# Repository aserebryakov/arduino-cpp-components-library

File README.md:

# Support Library for Arduino Devices

## Overview

This library is meant to provide different options to use Arduino or other compatible controllers and integrate use of
different devices (rotary encoders, buttons, switches).

## Abstraction Levels

There are following levels of abstractions:

  1. Raw API
  2. Support library hardware API facade
  3. Pins
  4. Components
  5. Devices

### Raw Arduino API

Direct usage of Arduino API functions like `pinMode()`, `digitalRead()` etc.

### Support library hardware API facade

This is a facade to isolate Arduino API calls.

It provides the possibility of mocking these interfaces for the purpose of components unit testing.

```mermaid
classDiagram
    class HwApi {
        <<interface>>
        + digitalRead(...)
        + digitalWrite(...)
        + pinMode(...)
    }
```

### Pins

Abstraction level that represents pins and work with them.

```mermaid
classDiagram
    direction BT
    class PinApi {
        <<interface>>
        + begin() = 0
        + loop() = 0
    }

    class DigitalInputPin {
        + begin()
        + loop()
    }

    class DigitalOutputPin {
        + begin()
        + loop()
    }

    class AnalogInputPin {
        + begin()
        + loop()
    }

    class AnalogOutputPin {
        + begin()
        + loop()
    }

    DigitalInputPin --|> PinApi : implements
    DigitalOutputPin --|> PinApi : implements
    AnalogInputPin --|> PinApi : implements
    AnalogOutputPin --|> PinApi : implements
```

### Components

Component is a composition of pins that has clear real life functional representation:

  * encoder
  * switch
  * button
  * etc.

```mermaid
classDiagram
    direction BT
    class Component {
        <<interface>>
        + begin() = 0
        + loop() = 0
    }
    
    class DigitalInputPin {
        + begin()
        + loop()
    }

    class Button {
        + begin()
        + loop()
    }

    class RotaryEncoder {
        + ctor(dt, clk, sw)
        + begin()
        + loop()
    }

    DigitalInputPin "1" --* "1" Button
    DigitalInputPin "3" --* "1" RotaryEncoder

    class DigitalOutputPin {
        + begin()
        + loop()
    }

    class Led {
        + begin()
        + loop()
    }

    DigitalOutputPin "1" --* "1" Led
    RotaryEncoder --|> Component : implements
    Led --|> Component : implements
    Button --|> Component : implements
```

### Devices

Device is a composition of components providing a specific functionality to user (e.g. volume control, gamepad, 
mouse, etc.).

```mermaid
classDiagram
    direction BT
    
    class Device {
        <<interface>>
        + begin() = 0
        + loop() = 0
    }
    
    class VolumeControl {
        + begin()
        + loop()
    }
    
    VolumeControl --|> Device : implements
    RotaryEncoder "1" --* "1" VolumeControl
```

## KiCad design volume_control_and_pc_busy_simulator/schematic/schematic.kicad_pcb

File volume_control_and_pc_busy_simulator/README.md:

# Volume Control with PC Busy

## Idea

To build a device that will contain following functionalities:

  * Volume control (volume up, volume down, mute)
  * Mouse move emulator
  * Keyboard input emulator

## User Interface

  * 5-pin rotary encoder to control volume
  * button to turn on/off mouse move emulation (with status LED)
  * button to turn on/off keyboard input emulation (with status LED)

### Software Design

```mermaid
---
title: Rotary Encoder
---
classDiagram
    class PIN_CHANGE {
        <<enumeration>>
        LOW_HIGH,
        HIGH_LOW,
        NO_CHANGE
    }

    class RotaryEncoderPin {
        <<interface>>
        + readPinChange() PIN_CHANGE
        + readPinStatus() bool
    }

    class RotaryEncoderPinImpl {
        + ctor(number, pin_mode)
    }

    class RotaryEncoderPinMock

    class RotaryEncoder {
        + ctor(dt_pin, clk_pin, sw_pin)
        + setTurnClockwiseHandler()
        + setTurnCounterClockwiseHandler()
        + setPushButtonHandler()
        + readStatus()
        - onClockwise
        - onCounterClockwise
        - onPushButton
        - dt_pin : RotaryEncoderPin
        - clk_pin : RotaryEncoderPin
        - sw_pin : RotaryEncoderPin
    }

    PIN_CHANGE --> RotaryEncoderPin

    RotaryEncoderPin <|-- RotaryEncoderPinImpl
    RotaryEncoderPin <|-- RotaryEncoderPinMock

    RotaryEncoder *-- RotaryEncoderPin
```

### Mouse Emulator Scheduling Example

```mermaid
sequenceDiagram
    participant Scheduler
    participant Controller
    participant RotaryEncoder
    participant MouseEmulator

    loop
        Controller ->> RotaryEncoder : readStatus()
        activate RotaryEncoder
        note over RotaryEncoder : call handlers
        RotaryEncoder -->> Controller : 
        deactivate RotaryEncoder

        Controller ->> MouseEmulator : readStatus()
        activate MouseEmulator

        alt START
            MouseEmulator -->> Controller : 
            Controller ->> Scheduler : addTask(mouse_callback)
            Scheduler -->> Controller : 
        else STOP
            MouseEmulator -->> Controller : 
            deactivate MouseEmulator
            Controller ->> Scheduler : removeTask(mouse_callback)
            Scheduler -->> Controller : 
        end
        
        Controller ->> Scheduler : tick(10ms)
        Scheduler -->> Controller : 
        
        note over Controller : delay(10ms)
    end
```

### Scheduler

```mermaid
sequenceDiagram
    participant Controller
    participant Scheduler

    Controller ->> Scheduler : addPeriodicTask(callback, period)

    Scheduler -->> Controller : task id
    note over Scheduler : store callback
    note over Scheduler : store period as time to next call

    Controller ->> Scheduler : tick(interval)
    note over Scheduler : substract value from task

    alt expired
        note over Scheduler : call callback and reset period
    else
        note over Scheduler : do nothing
    end

    Scheduler -->> Controller : 
```

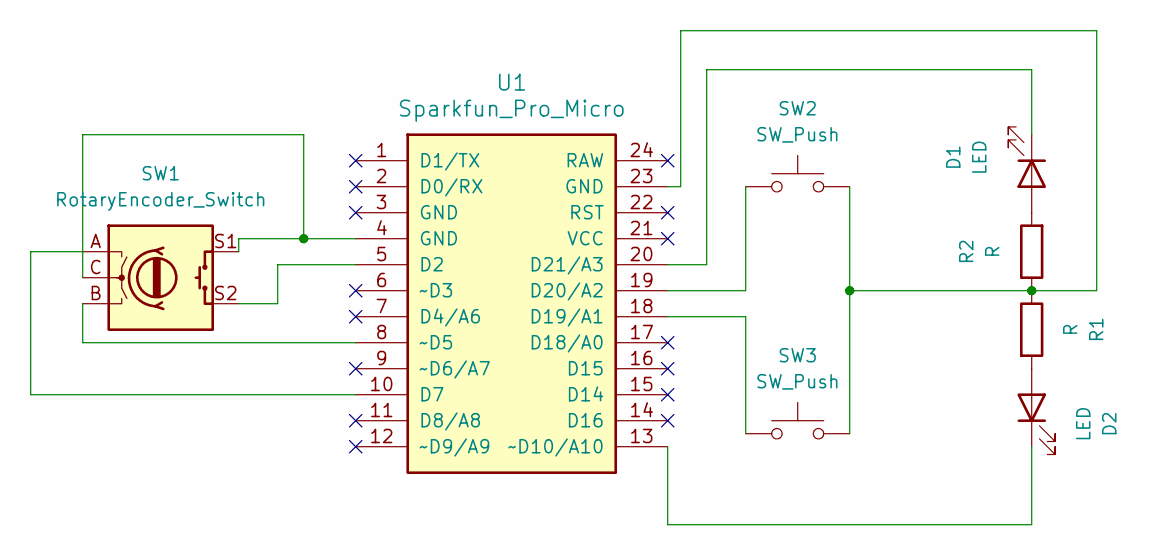
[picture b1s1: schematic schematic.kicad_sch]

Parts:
D1, D2: LED; LED_D5.0mm
R1, R2: R; R_Axial_DIN0207_L6.3mm_D2.5mm_P7.62mm_Horizontal
SW1: RotaryEncoder_Switch; RotaryEncoder_Alps_EC12E-Switch_Vertical_H20mm
SW2, SW3: SW_Push; SW_PUSH_6mm_H5mm
U1: Sparkfun_Pro_Micro

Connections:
unnamed: D1.2 (A), R2.2
unnamed: D1.1 (K), U1.20 (D21/A3)
unnamed: D2.2 (A), R1.2
unnamed: D2.1 (K), U1.13 (~D10/A10)
unnamed: R1.1, R2.1, SW2.2, SW3.2, U1.23 (GND)
unnamed: SW1.C, SW1.S1, U1.4 (GND)
unnamed: SW1.S2, U1.5 (D2)
unnamed: SW1.A, U1.10 (D7)
unnamed: SW3.1, U1.18 (D19/A1)
unnamed: SW2.1, U1.19 (D20/A2)
unnamed: SW1.B, U1.8 (~D5)

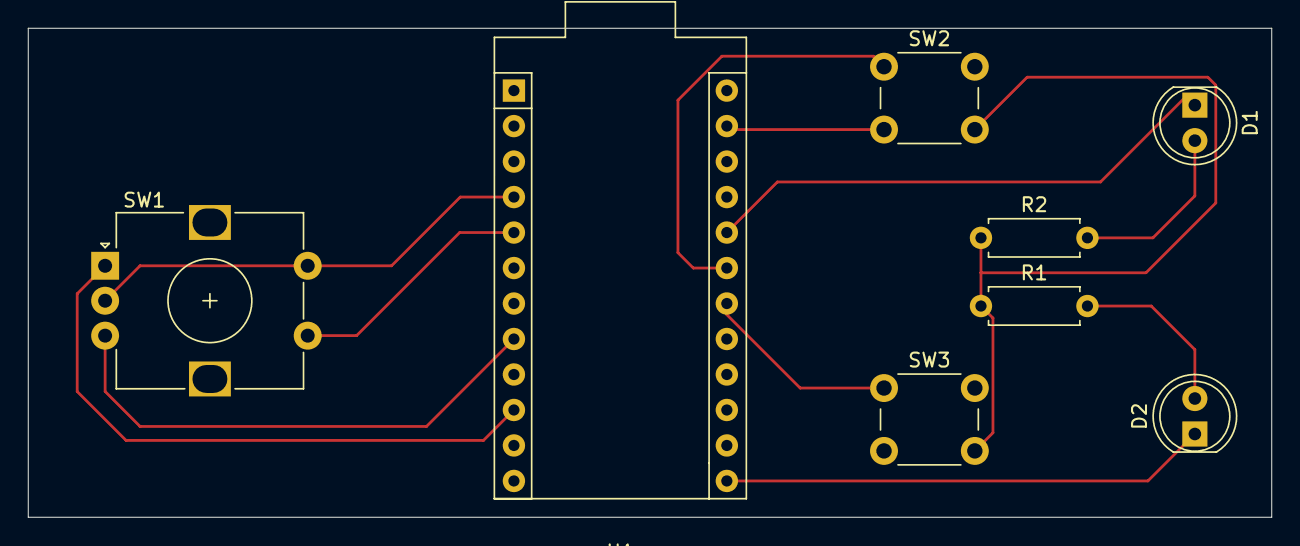
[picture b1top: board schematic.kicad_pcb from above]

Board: 2 copper layers, 89.0 x 35.0 mm, 8 parts (0 on the bottom side), 11 nets.

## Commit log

2024-09-04 First prototype of traffic light project
2024-09-04 Changed algorithm to scheduled execution, but there's no blinking green at the moment.
2024-09-05 Implemented blinking. It works, but code doesn't look C++ at all.
2024-09-07 Implements potentiometer based duration regulation
2024-09-11 Prototype of rotary encoder
2024-09-11 VolumeControl: Working prototype of rotary encoder
2024-09-11 VolumeControl: Adds README
2024-09-11 VolumeControl: Updates RotaryEncoder class diagram
2024-09-11 VolumeControl: Rough design of mouse emulator enabling/disabling
2024-09-11 VolumeControl: Added tick for scheduler
2024-09-11 VolumeControl: Fixed diagram rendering
2024-09-11 VolumeControl: Adds a rough overview on scheduling process
2024-09-12 Adding support library for projects
2024-09-12 Scheduler: Added example test
2024-09-12 SupportLibrary: Basic integration with Arduino IDE
2024-09-12 Scheduler: adds basic scheduling
2024-09-12 Scheduler: Implements task removal but it will be a mess if tasks are removed in wrong order
2024-09-12 Scheduler: Fixes task removal
2024-09-12 Infrastructure: Moved tests to a separate directory
2024-09-14 SupportLibrary: Adds rotary encoder class stub
2024-09-14 RotaryEncoder: Implements turn clockwise support
2024-09-14 RotaryEncoder: Complete implementation of encoder logic
2024-09-14 VolumeControl: First try of new infrastructure
2024-09-14 RotaryEncoder: Fixes early return
2024-09-14 VolumeControl: complete migration to new infrastructure
2024-09-15 SupportLibrary: Adds HW API interface to encapsulate even more functionality in the library
2024-09-15 SupportLibrary: Adds hardware API encapsulation
2024-09-15 RotaryEncoder: Made rotary pins to be read the same time
2024-09-15 RotaryEncoder: Updated API to remove need of creating individual pins
2024-09-15 VolumeControl: Mouse move prototype
2024-09-15 MouseControl: Imporved mouse control
2024-09-15 VolumeControl: Added keyboard functionality and indicators leds (terribly looking code)
2024-09-16 VolumeControl: Added schematics and updated pins in accordance
2024-09-19 HwApi: Fixes level underlying type
2024-09-19 VolumeControl: Dirty fix not to make buttons turned off in the beginning
2024-09-19 VolumeControl: Schematic update
2024-09-19 CustomMidi: Just a working example copy
2024-09-19 CustomMidi: Made it work with potentiometer
2024-09-19 CustomMidi: Added buttons
2024-09-20 CustomMidi: Limits playing note range
2024-09-20 CustomMidi: Adds schematics
2024-09-30 HwApi: DigitalPin: Reworks digital pin API for better clarity
2024-10-03 VolumeControl: Makes steps bigger for volume control
2024-10-03 DcsControl: New rotary encoder test
2024-10-03 DcsControl: Powered encoder doesn't seem to work with current implementation
2024-10-03 DcsControl: Adds the schematic
2024-10-04 DcsControl: Encoder prototype.
2024-10-10 SupportLibrary: Better naming
2024-10-10 DigitalPin: Changes default pin level to LEVEL_HIGH
2024-10-10 RotaryEncoder: API update for better naming
2024-10-10 DcsControl: Schematics update
2024-10-11 DcsControl: Implements rotary encoders
2024-10-20 DcsControl: Adds all the switched
2024-10-21 DcsControl: Extract pressButton function
2024-10-30 DcsControl: Renaming and adding README stub
2024-10-31 DcsControl: Updated schematics and exported all symbols to a library
2024-10-31 DcsControl: Assembly instructions and schematics update
2024-11-05 DcsControl: Added screws size to instruction
2024-11-05 DeviceBuilder: Some wide ideas
2024-11-05 ControllerBuilder: Minimalistic POC for generic construction
2024-11-07 Added HeapObject that has similar functionality to std::unique_ptr
2024-11-07 ControlBuilder: Replaced instance with HeapObject
2024-11-07 Controller: Some more wip thoughts about the controller structure.
2024-11-07 GenericControl: Extended tests
2024-11-07 GenericController: Adds setup() interface
2024-11-08 GeneticController: Added loop() implementation
2024-11-19 DitigalPin: Adopted to use Control API
2024-11-19 Control: Extracted to a separate file
2024-11-19 RotaryEncoder: Adapted rotary encorder API
2024-11-19 API: Changed pin modes names because of conflict with define
2024-11-20 VolumeControl: Adopted MouseControl to use new infrastructure.
2024-11-21 VolumeControl: Completely reworked to comply the API
2024-11-21 Peripherals: POC for peripherals library structure
2024-11-21 API: Renamed API to be more descriptive
2024-11-28 API: Further api polishing
2024-11-28 Peripherals: Moved things but it doesn't link
2024-11-28 API: Changed files structure to be conformant with arduino libraries.
    Linker fails
2024-11-29 API: Moved everything to a single library
2024-12-05 Peripherals: Ugly hack to make it build.
    The problem is the following:
    HID-Project library requires dot_a_linkage=true in properties to work
    (don't know the reason at the moment).
    The peripherals library must be dependent on HID-Project.
    When trying to link the following error appear:
    ```
2024-12-05 API: Changes function names to comply Arduino style recommendations
2024-12-05 API: Fixes template function definition to stop generate warning
2024-12-05 Peripherals: Moved mouse control to library
2024-12-08 Design: Reworked the design document for better abstraction levels separation
2024-12-08 API: Massive rework in accordance to design
2024-12-08 API: Better naming
2024-12-08 API: Moving everything back to flat structure because of need either to set two different includes if files are split up to directories (Arduino IDE limitation)
2024-12-08 Components: Implemented Button, updated DigitalInputPin hiding possibility of configuration as OUTPUT
2024-12-09 Peripherals: Updated the mouse control to new API
2024-12-09 Pins: Added DigitalOutputPin
2024-12-09 Components: Adds DigitalLed
2024-12-09 VolumeControl: Connected indicator led
2024-12-12 FlightsimController: Completely reworked code to a new API
2024-12-12 Device functionality switch POC
2024-12-15 Controller: Added a consumer HID button tester (requires Serial connection to see which button is pressed)
2024-12-15 Controller: Scheme: Updated schematics to connect SW1 pin with RST on controller
2024-12-15 VolumeControl: Restored keyboard functionality
2024-12-15 Peripherals: Moved MouseControl to device code because it has specific for it connections between components.
2024-12-15 Controller: Integrated Mouse and Keyboard activity emulation to controller
2024-12-19 Leaving only library code
2024-12-19 Updated library properties
2024-12-22 Library: Adds primary header and changes library name as per ArduinoLint recommendations
2024-12-24 Infrastructure: I can't change library name anymore
2024-12-24 Infrastructure: Updated main library header
2024-12-24 Documentation: Updates diagrams to be properly oriented and correspond namings in the code
2025-01-14 Infrastructure: Fixes compilation error
2025-01-15 Examples: Adds the Rotary Encoder example
2025-01-16 RotaryEncoder: Fixes incorrect callback calls. Pins were swapped. Closes #1
2025-01-16 CI: Create cmake-multi-platform.yml
2025-01-16 CI: remove windows builds
2025-01-16 CI: removing windows build from matrix
2025-01-16 Infrastructure: Updates CMake files to enable ctest
2025-01-16 CI: Adds ArduinoLint job
2025-01-16 CI: removes 'strict' from ArduinoLint until library naming will not be fixed
2025-01-16 Versioning: Fixes library version in library.properties
2025-01-16 Examples: Added necessary comments to RotaryEncoder example. Closes #3.
2025-01-16 Examples: Adds Button example. Closes #5.
2025-01-16 Examples: Adds Digital LED example. Closes #6.
2025-01-16 Library: version increment
2026-01-31 Adds AnalogInputPin
2026-02-17 Added AnalogInputPin
2026-02-18 Added AnalogLed
2026-02-22 Adds Potentiometer (vibe coded)
2026-02-23 Fix the integer overflow in mapping function
2026-03-07 Rename Potentiometer to AnalogInput and make Potentiometer an alias of AnalogInput
2026-03-07 Version update in library.properties
2026-03-10 Fixes compilation error for ESP32 caused by pin modes defines mismatch with Arduino
2026-03-18 Adds Joystick component
2026-03-18 Joystick example draft
